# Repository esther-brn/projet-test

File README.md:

# 4GP 2024/2025 - Projet de capteur *low-tech en graphite* - Par Esther BOIRON et Margot HERNANDEZ
-------------------------

## Table des matières
* [Contacts](#contacts) 
* [Contexte](#contexte) 
* [Livrable](#livrable) 
* [Matériel requis](#matériel-requis) <br>
* [1. Simulation électronique sous LTSpice](#1-simulation-électronique-sous-ltspice) <br>
* [2. Design du PCB sous Kicad](#2-design-du-pcb-sous-kicad) <br>
* [3. Code sur Arduino](#3-code-sur-arduino) <br>
* [4. Application Android](#4-application-android) <br>
* [5. Réalisation du shield](#5-réalisation-du-shield) <br>
* [6. Banc de tests](#6-banc-de-tests) <br>
* [7. Résultats et discussion](#7-résultats-et-discussion) <br>
* [8. Datasheet du capteur](#8-datasheet-du-capteur) 
* [Conclusion](#conclusion)
------------
## Contacts
Esther BOIRON : eboiron@insa-toulouse.fr  
Margot HERNANDEZ : mhernan2@insa-toulouse.fr

------------
## Contexte
Dans le cadre de l’UF de quatrième année du département Génie Physique intitulée *Du capteur au banc de test*, nous avons développé et évalué la performance d’un capteur low-tech en graphite. Il est constitué d’un simple morceau de papier recouvert d’une trace de crayon à papier, formant une fine couche de graphite. Lorsque le papier se déforme, le nombre de particules de graphite reliées varie, entraînant une modification de la résistance du capteur. Ce phénomène permet ainsi de mesurer la déformation, à la manière d’une jauge de contrainte traditionnelle.

Ce travail s’appuie sur les recherches de scientifiques américains (Cheng-Wei Lin*, Zhibo Zhao*, Jaemyung Kim & Jiaxing Huang), qui ont publié en 2014 l’article [Pencil Drawn Strain Gauges and Chemiresistors on Paper](https://www.researchgate.net/publication/259846610_Pencil_Drawn_Strain_Gauges_and_Chemiresistors_on_Paper).

Vous trouverez ici l’ensemble des réalisations effectuées dans le cadre de ce projet : simulations électroniques, conception du PCB, programmation Arduino, développement d’une application Android et élaboration d’une datasheet.

------------
## Livrable
Plusieurs livrables sont attendus :

✓ Un shield PCB connecté à une carte Arduino UNO, intégrant : un capteur en graphite, un montage amplificateur transimpédance, un module Bluetooth, un écran OLED, un encodeur rotatif, un potentiomètre numérique ainsi qu'un capteur de flexion commercial (flex sensor).<br>

✓ Un code Arduino assurant le contrôle de l’ensemble des composants et la réalisation des mesures.<br>

✓ Une application Android permettant de visualiser les mesures depuis un smartphone.<br>

✓ Un code Arduino dédié aux essais du capteur sur le banc de test.<br>

✓ Une datasheet détaillant les caractéristiques du capteur en graphite.<br>

------------
## Matériel requis
Afin de réaliser notre dispositif, voici la liste des composants nécessaires :

Pour le montage amplificateur transimpédance :

* Des résistances : 1 de 1 kΩ, 1 de 10 kΩ, 2 de 100 kΩ
* Un potentiomètre numérique : ici, le MCP41050
* Des condensateurs : trois de 100 nF et un de 1 μF
* Un amplificateur opérationnel : ici, le LTC1050

Pour le reste du dispositif :
* Un module Bluetooth : ici, le HC05
* Un écran OLED : ici, un écran de dimensions 128x64
* Un encodeur rotatif
* Un capteur de flexion (flex sensor)
* Une résistance de 33 kΩ
* Une carte Arduino UNO
------------
## 1. Simulation électronique sous LTSpice
Notre objectif est de mesurer la résistance de notre capteur en graphite puis de retrouver sa déformation par une relation de proportionalité. Nous savons que la résistance est de l’ordre du gigaohm (GΩ). Sous une tension de 5V, correspondant à celle délivrée par l’Arduino, le capteur délivre un courant extrêmement faible, de l’ordre de quelques nanoampères (nA). Cette mesure ne peut donc pas se faire directement : nous devons amplifier le signal. De plus, nous utilisons l'Arduino Uno et ce microcontrôleur ne peut mesurer que des tensions (cf [datasheet](https://docs.arduino.cc/resources/datasheets/A000066-datasheet.pdf)). Nous avons donc besoin d'un montage amplificateur transimpédance pour convertir notre courant en une tension exploitable par les entrées analogiques de l'Arduino. Pour cela, nous avons choisi l’amplificateur opérationnel  LTC1050.

Associé à cet amplificateur, nous réalisons un montage structuré en trois zones principales qui correspondent à des filtres pour améliorer la qualité du signal mesuré :

* Filtrage en entrée de l'amplificateur (R1 et C1) : un filtre passe-bas passif de fréquence de coupure de 16 Hz qui permet de filtrer le bruit en courant sur le signal d'entrée
* Filtrage couplé à l'amplificateur (R3 et C4) : un filtre passe-bas actif de fréquence de coupure de 1.6 Hz qui permet de filtrer la composante 50 Hz issue du réseau électrique 
* Filtrage à la sortie de l'amplificateur (R6 et C2) : filtre passe bas passif de fréquence de coupure de 1.6 kHz qui permet de réduire le bruit créé lors du traitement du signal (bruits des alimentations, de l’horloge…)

Afin de pouvoir ajuster dynamiquement le gain de l’amplificateur en fonction des besoins de mesure, la résistance R2 sera remplacée ultérieurement par un potentiomètre digital.

Nous avons validé notre montage sur LTSpice en deux étapes :

Tout d'abord, nous avons réalisé une première simulation afin de s’assurer que l’amplification fonctionne correctement. L’image ci-dessous montre que le signal est bien amplifié à 1 V : le signal a donc une valeur suffisante pour être interprété par l’Arduino.

Ensuite, nous avons réalisé une seconde simulation afin d'observer la réponse à un courant alternatif afin de vérifier l’efficacité du filtrage. Les variations de la phase observées sur le graphe ci-dessous illustrent le passage du signal à travers les trois filtres successifs.

------------
## 2. Design du PCB sous Kicad
Après avoir réalisé les simulations sur LTSpice, nous avons conçu notre PCB à l’aide du logiciel KiCad. Pour cela, nous sommes parties du schéma du montage décrit précédemment, auquel nous avons apporté quelques modifications.
Parmi ces modifications, nous avons notamment remplacé la résistance R2 par un potentiomètre numérique permettant un réglage précis du gain de l’amplificateur, tout en évitant la saturation. Nous avons également ajouté plusieurs composants afin d’améliorer les fonctionnalités de notre système et de comparer les résultats obtenus :
* Le module Bluetooth HC-05 : permet d'assurer la communication entre le PCB et un smartphone via une application Android.
* Un écran OLED : utilisé pour afficher différents menus en temps réel.
* Un encodeur rotatif : contrôle la navigation entre les différentes options affichées sur l’écran OLED.
* Un flex sensor : utilisé pour comparer les mesures du capteur en graphite avec celles d’un capteur commercial lors des tests finaux

__Création des bibliothèques et symboles__  

La première étape de la conception a consisté à créer notre propre bibliothèque de symboles pour les composants spécifiques du montage. Nous avons dessiné les symboles correspondants aux différents composants utilisés. L’image ci-dessous illustre, par exemple, le symbole de l’écran OLED.

__Création des empreintes des composants__

La deuxième étape a consisté à créer les empreintes des composants. Cette phase est essentielle pour garantir une bonne intégration des composants sur le circuit imprimé. Pour cela, nous avons pris en compte la dimension physique des composants ainsi que le diamètre des trous. L’image ci-dessous illustre l’empreinte de l’écran OLED.

Afin d’obtenir une visualisation 3D réaliste de notre PCB final, nous avons associé à chaque empreinte une modélisation 3D du composant correspondant. Cette étape permet de vérifier l’agencement des composants, d’anticiper d’éventuels problèmes d’encombrement et d’optimiser le design du circuit imprimé.
Les modèles 3D utilisés ont été récupérés sur la plateforme GrabCAD, qui propose une large bibliothèque de fichiers compatibles avec KiCad.
L’image ci-dessous illustre la modélisation 3D de l’écran OLED.

__Création de la schématique électrique__

Après avoir défini les empreintes et les modèles 3D des composants, nous avons procédé à la création de la schématique électrique du montage. Lors de cette étape, nous avons opté pour un modèle basé sur l’Arduino UNO afin de garantir la correspondance correcte des pins de connexion avec l’Arduino.

__Disposition des composants sur le PCB__

La dernière étape de notre conception a été l’agencement des composants sur le PCB. L’objectif principal est d’optimiser leur disposition en tenant compte des connexions électriques tout en minimisant l’utilisation de vias. Les images ci-dessous présentent le résultat final de notre PCB, ainsi que sa vue en 3D, permettant de visualiser l’implantation des composants.

------------
## 3. Code sur Arduino
Notre code Arduino, conçu pour contrôler les composants implémentés et effectuer les mesures à l’aide du capteur en graphite et du capteur commercial, a été développé sous [Arduino IDE 2.3.4](https://www.arduino.cc/en/software/).  

Nous avons utilisé les bibliothèques *SoftwareSerial.h* pour la communication Bluetooth et *Adafruit_SSD1306.h* pour l'affichage sur écran OLED. Étant donné que notre programme utilise une part importante de la mémoire RAM, nous avons rencontré des problèmes de stockage : le programme ne se lançait pas et aucune information n'était affichée dans l'IDE lors du téléversement. Pour remédier à cela, nous avons intégré la bibliothèque *avr/pgmspace.h*, qui permet de stocker des données en mémoire flash afin de libérer de l’espace dans la RAM. 

Nous avons réalise un premier programme qui permet de calibrer le potentiomètre digitale afin d’optimiser les mesures réalisées par les deux capteurs. Le programme principal propose une interface à l’écran avec quatre menus, accessibles en tournant l’encodeur rotatif. La sélection d’un menu se fait en appuyant sur le bouton intégré à l’encodeur. Ce bouton permet également de revenir au menu principal lorsque nous sommes dans un sous-menu.  

Les sous-menus disponibles sont les suivants :
* Menu Informations : fournit des détails sur le projet.
* Menu Application : permet d'établir une communication avec l’application Android via le module Bluetooth.
* Menu Capteur Graphite : affiche en temps réel la valeur de résistance mesurée par le capteur en graphite.
* Menu Capteur Commercial : affiche en temps réel la valeur de résistance mesurée par le capteur commercial.<br>

Les codes complets sont disponibles dans le dossier [Arduino](Arduino).

Ci-dessous, une vidéo illustrant les différents menus accessibles sur l’écran OLED :

------------
## 4. Application Android
Nous avons également réalisé une application Android développée sous [MIT App Inventor](https://appinventor.mit.edu/).

Cette application reçoit les données transmises par le module Bluetooth HC-05 lorsque l’utilisateur est dans le mode « application » de l’écran OLED accessible via l’encodeur rotatif. 

Deux modes sont disponibles à partir d’un listpicker : le mode « capteur graphite » et le mode « capteur commercial ». Dans chacun de ces modes, la valeur de la résistance du capteur est affichée en temps réel. En cliquant sur le bouton « start », l’application passe en mode acquisition et trace l’évolution de la résistance sur un graphique en fonction du temps. L’acquisition est arrêtée en cliquant sur « pause ». Le bouton refresh permet de réinitialiser le graphique en effaçant les données précédemment tracées.

L’application ainsi que son code source sont disponibles dans le répertoire [Application](Application).

------------
## 5. Réalisation du shield
Après la conception et la validation du PCB, nous avons procédé à la fabrication physique du shield en suivant plusieurs étapes :
* Vérification du PCB sur KiCad : utilisation de l’outil Contrôle des règles de conception (DRC) pour s’assurer qu’il n’y a pas d’erreur dans les connexions et les espacements des pistes.
* Impression du masque de gravure sur un papier transparent 
* Insolation UV d’une plaquette d’époxy recouverte d’une couche de cuivre et de résine photosensible : la plaquette est exposée aux UV à travers le masque
* Révélation du motif : la plaquette est immergée dans un révélateur (soude très diluée) afin d'éliminer la résine exposée aux UV et laisser les pistes de cuivre protégées 
* Gravure des pistes : la plaquette est immergée dans un bain de perchlorure de fer pour graver les pistes
* Nettoyage de la plaquette : utilisation d'acétone pour retirer les résidus de résine 
* Perçage des trous et soudure des composants sur le PCB

------------
## 6. Banc de tests
Le but de ce banc de test est de déterminer la sensibilité du capteur, d’étudier son évolution, puis de la comparer à celle d’un capteur commercial de type "Flex-Sensor". Pour cela, nous avons utilisé le banc de test suivant, composé de six cercles dont les diamètres varient de 1.4 à 3.9 cm. Ce banc a été fabriqué à l’aide d’une imprimante 3D.

Ce banc de test permet de mesurer la variation de résistance relative ΔR/R0 en fonction de la déformation ε, définie par la relation ε =e/D où e est l'épaisseur du capteur (ici celle de la feuille, soit 0,2 mm) et D le diamètre du cercle considéré.  

Les tests ont été réalisés en tension et en compression sur des capteurs à base de graphite.

Ces capteurs ont été fabriqués à l’aide de quatre types de graphite différents : des crayons 6B, 4B, B et HB. Pour maintenir les capteurs en papier sur le banc de test sans les toucher pendant les mesures, nous avons utilisé de la pâte à fixe.

------------
## 7. Résultats et discussion
Les courbes ci-dessous illustrent les variations de la résistance en fonction de la déformation, en tension et en compression, pour des capteurs en graphite réalisés avec différents types de crayons. 

La courbe ci-dessous présente le comportement du capteur commercial pour une déformation en tension, le flex sensor ne supportant pas une déformation en compression. 

On remarque que lorsque le capteur graphite est soumis à une déformation en tension, la résistance du capteur augmente. Ce phénomène est attendu : en tension, les distances entre les nanoparticules de graphite s’allongent, ce qui freine le passage du courant et augmente la résistance. A l’inverse, lors d’une compression, les grains se rapprochent, facilitant le passage du courant et donc la résistance diminue.  

Les résultats montrent aussi que le type de crayon utilisé influence fortement les valeurs de résistance mesurées. Plus un crayon est gras (comme le 6B ou le 4B), plus il dépose de graphite sur le papier, ce qui réduit la résistance globale du capteur. Les courbes indiquent également que plus un crayon est gras, moins la variation relative de la résistance est importante. Autrement dit, les capteurs réalisés avec des crayons plus gras sont moins sensibles à la déformation.  

Ces résultats expérimentaux permettent de conclure que le capteur commercial est globalement plus sensible à la déformation que les capteurs en graphite. De plus, il présente une bien meilleure robustesse : les capteurs en graphite sont fragiles et le simple fait de toucher leur surface peut altérer le dépôt de graphite, faussant les mesures qui suivent. Il faut les manipuler avec beaucoup de précaution. Leur durée de vie est aussi limitée, en particulier lorsqu’ils sont soumis à de fortes déformations. Entre chaque série de tests (tension ou compression), il a été nécessaire de fabriquer un nouveau capteur, car la résistance au repos changeait significativement après les premières déformations.  

Il est important de noter que plusieurs facteurs peuvent influencer les résultats, notamment la quantité de graphite déposée sur le papier, qui est difficile à maîtriser précisément. Cette variabilité peut entraîner des écarts non négligeables dans les mesures. Une amélioration possible consisterait à développer un procédé de dépôt de graphite d’une quantité fixe et reproductible, ainsi qu’un système de protection de la face du capteur contenant le trait de graphite pour éviter la perte de matière au contact.  

Le capteur commercial s'avère donc plus précis, plus robuste, et mieux adapté à des mesures répétées ou à des déformations importantes. En revanche, les capteurs en graphite présentent l’avantage de pouvoir mesurer des déformations en compression, contrairement au flex-sensor.

------------
## 8. Datasheet du capteur
Vous pouvez trouver la datasheet du capteur [ici](Datasheet.pdf).

------------
## Conclusion
Ce projet a été très enrichissant, nous offrant une immersion concrète dans le métier d’ingénieur, avec des tâches variées allant des phases de simulation jusqu’à la rédaction d’une datasheet. Nous avons apprécié la diversité des compétences mobilisées : conception électronique, fabrication, expérimentation et analyse, ainsi que la satisfaction de voir aboutir un produit final fonctionnel.  

Le capteur que nous avons développé est opérationnel et les tests réalisés mettent en évidence des tendances globalement cohérentes avec les principes physiques attendus. Ces résultats montrent qu’un simple matériau comme le graphite peut être exploité pour détecter des déformations mécaniques.  

Cependant, les conditions expérimentales mises en œuvre restent assez artisanales et peu reproductibles. La précision des mesures est fortement influencée par des paramètres difficilement maîtrisables, tels que la quantité de graphite déposée ou la qualité du contact des pinces sur les traits de crayon du capteur. De plus, la fragilité du capteur et sa très faible durée de vie rendent son industrialisation peu envisageable.

<br><br><br><br><br>

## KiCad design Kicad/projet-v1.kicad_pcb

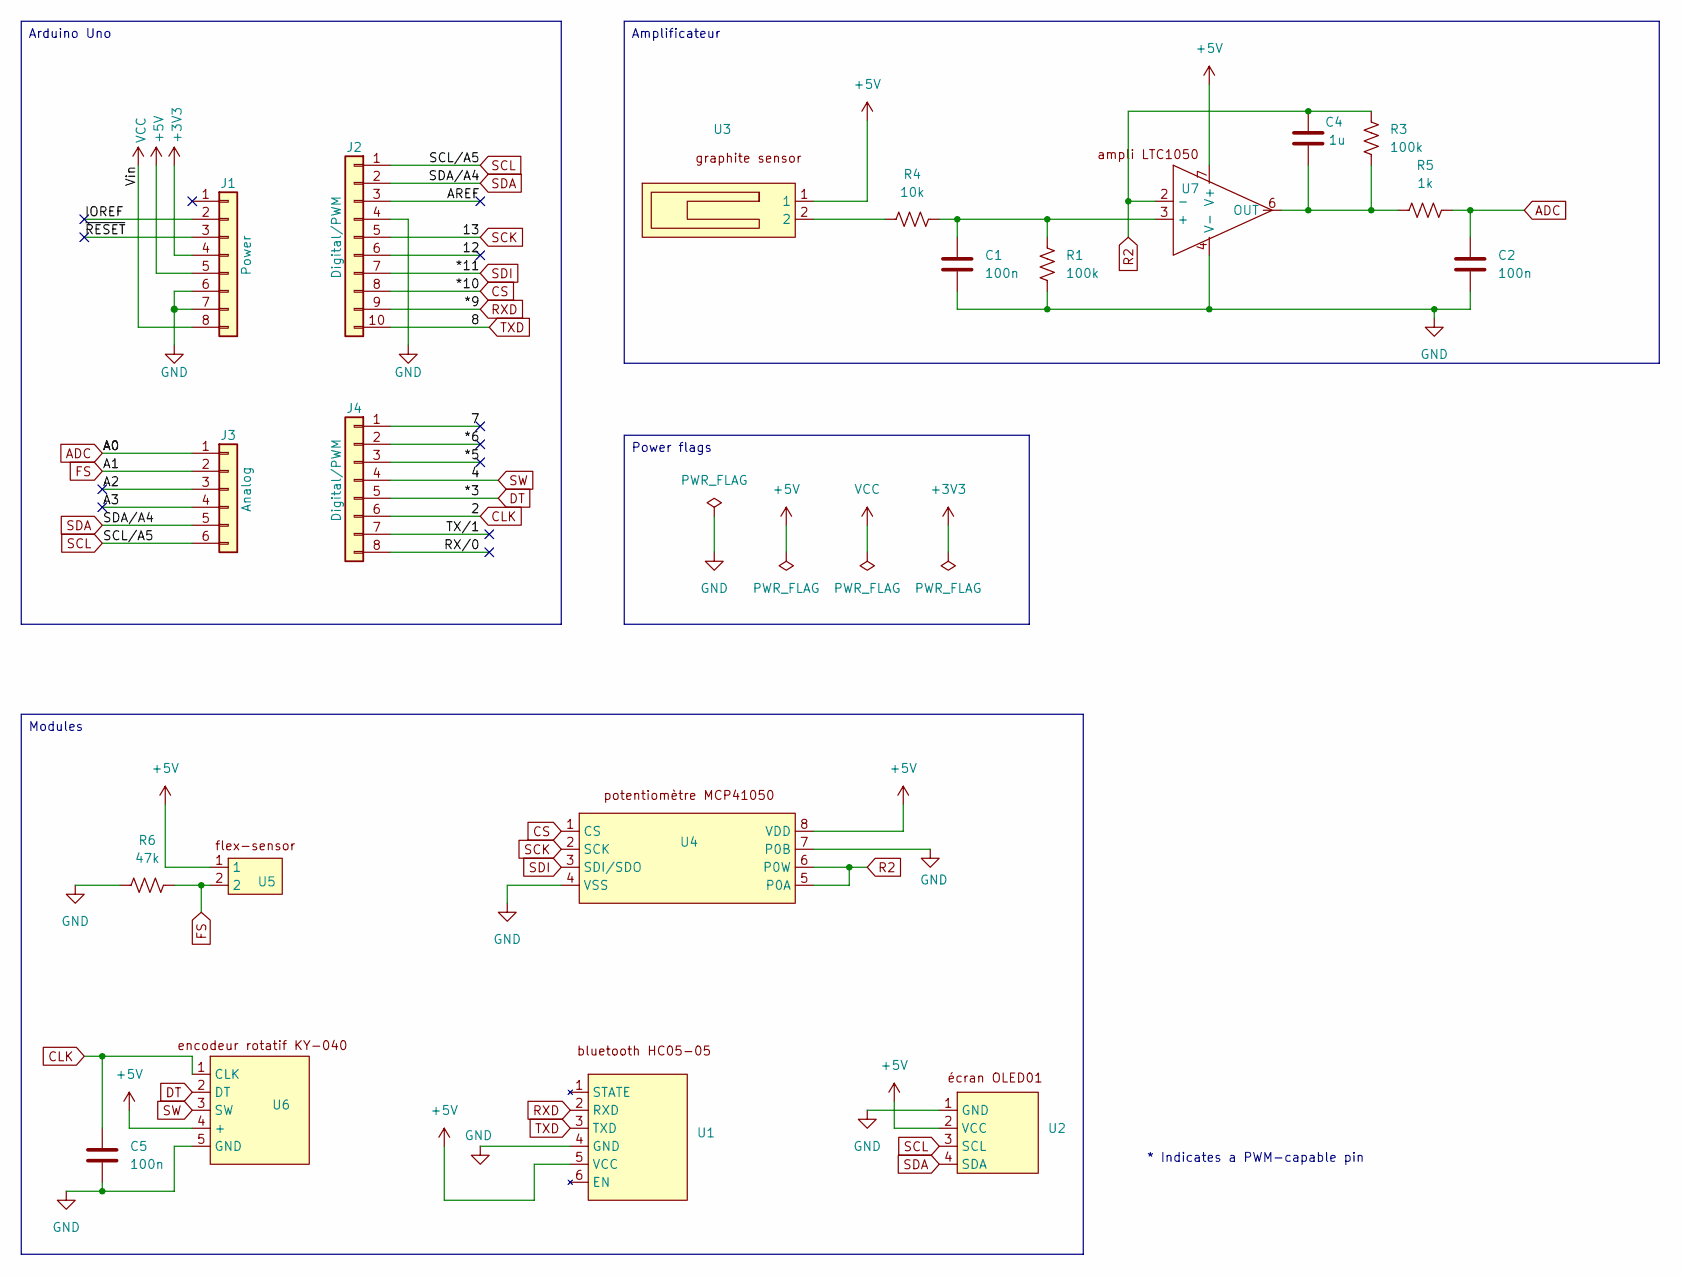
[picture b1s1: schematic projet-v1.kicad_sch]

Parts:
C1, C2, C5: 100n; C_Disc_D4.7mm_W2.5mm_P5.00mm
C4: 1u; C_Rect_L7.0mm_W4.5mm_P5.00mm
J1: Power; PinSocket_1x08_P2.54mm_Vertical
J2: Digital/PWM; PinSocket_1x10_P2.54mm_Vertical
J3: Analog; PinSocket_1x06_P2.54mm_Vertical
J4: Digital/PWM; PinSocket_1x08_P2.54mm_Vertical
R1, R3: 100k; R_Axial_DIN0207_L6.3mm_D2.5mm_P5.08mm_Vertical
R4: 10k; R_Axial_DIN0207_L6.3mm_D2.5mm_P5.08mm_Vertical
R5: 1k; R_Axial_DIN0207_L6.3mm_D2.5mm_P5.08mm_Vertical
R6: 47k; R_Axial_DIN0207_L6.3mm_D2.5mm_P5.08mm_Vertical
U1: HC05-05
U2: OLED01
U3: graphite-sensor
U4: MCP41050
U5: flex-sensor
U6: KY-040
U7: LTC1050

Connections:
+3V3: J1.4
+5V: J1.5, U1.5 (VCC), U2.2 (VCC), U3.1, U4.8 (VDD), U5.1, U6.4 (+), U7.7 (V+)
/7: J4.1
/12: J2.6
/*5: J4.3
/*6: J4.2
/A2: J3.3
/A3: J3.4
/AREF: J2.3
/IOREF: J1.2
/RX/0: J4.8
/TX/1: J4.7
/~RESET: J1.3
ADC: C2.1, J3.1, R5.2
CLK: C5.1, J4.6, U6.1 (CLK)
CS: J2.8, U4.1 (CS)
DT: J4.5, U6.2 (DT)
FS: J3.2, R6.2, U5.2
GND: C1.2, C2.2, C5.2, J1.6, J1.7, J2.4, R1.2, R6.1, U1.4 (GND), U2.1 (GND), U4.4 (VSS), U4.7 (P0B), U6.5 (GND), U7.4 (V-)
unnamed: R4.1, U3.2
unnamed: C1.1, R1.1, R4.2, U7.3 (+)
unnamed: C4.2, R3.2, R5.1, U7.6 (OUT)
R2: C4.1, R3.1, U4.5 (P0A), U4.6 (P0W), U7.2 (-)
RXD: J2.9, U1.2 (RXD)
SCK: J2.5, U4.2 (SCK)
SCL: J2.1, J3.6, U2.3 (SCL)
SDA: J2.2, J3.5, U2.4 (SDA)
SDI: J2.7, U4.3 (SDI/SDO)
SW: J4.4, U6.3 (SW)
TXD: J2.10, U1.3 (TXD)
VCC: J1.8

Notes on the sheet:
* Indicates a PWM-capable pin
Power flags
Amplificateur
Arduino Uno
Modules

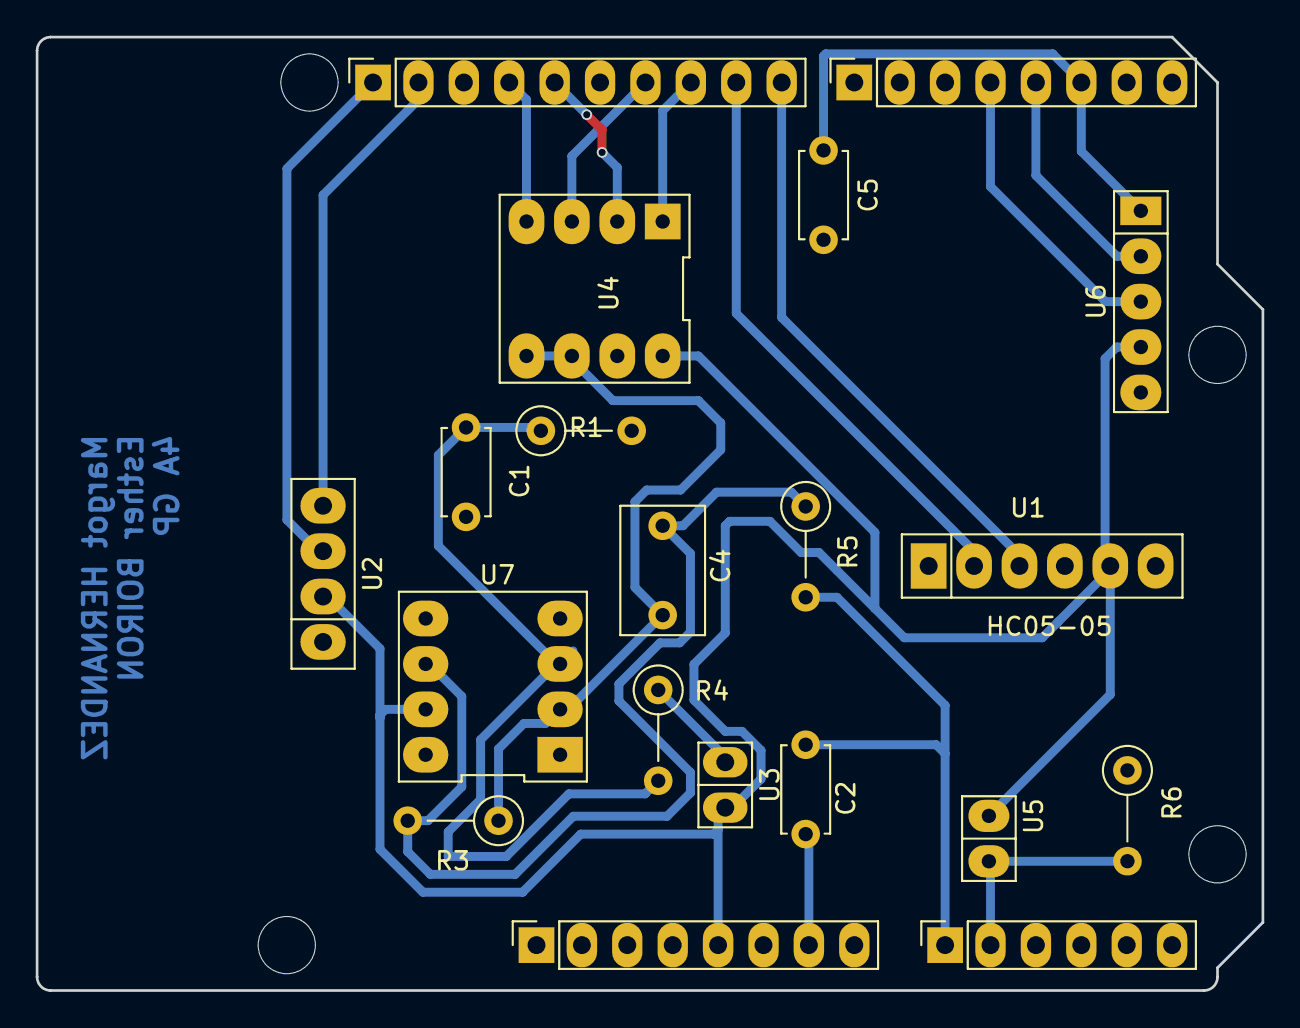
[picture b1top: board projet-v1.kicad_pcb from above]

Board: 2 copper layers, 68.6 x 53.3 mm, 24 parts (0 on the bottom side), 18 nets.

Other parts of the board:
MH1, MH2, MH3, MH4: MountingHole_3.2mm

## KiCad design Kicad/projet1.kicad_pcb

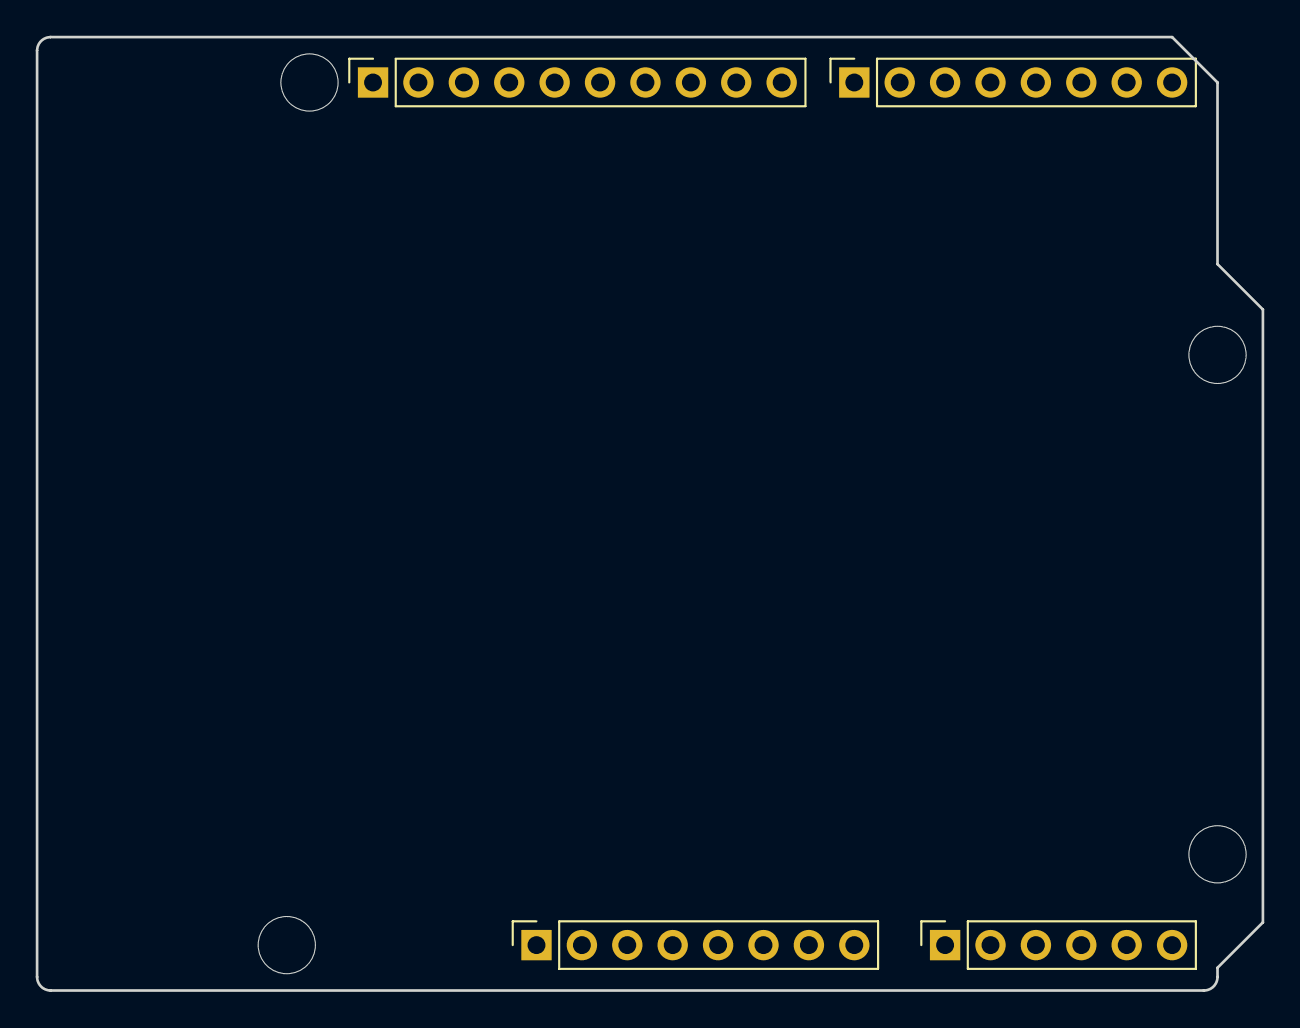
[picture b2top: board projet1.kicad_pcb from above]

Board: 2 copper layers, 68.6 x 53.3 mm, 8 parts (0 on the bottom side), 3 nets, no tracks yet.

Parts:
J1: Power; PinSocket_1x08_P2.54mm_Vertical
J2: Digital/PWM; PinSocket_1x10_P2.54mm_Vertical
J3: Analog; PinSocket_1x06_P2.54mm_Vertical
J4: Digital/PWM; PinSocket_1x08_P2.54mm_Vertical
MH1, MH2, MH3, MH4: MountingHole_3.2mm

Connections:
/SCL/A5: J2.1, J3.6
/SDA/A4: J2.2, J3.5
GND: J1.6, J1.7, J2.4

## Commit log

2025-03-20 Premier commit
2025-03-20 MAJ README.md
2025-03-23 MAJ dossier image
2025-03-23 MAJ README v2
2025-03-26 MAJ README v3
2025-04-06 MAJ README v4
2025-04-08 MAJ README v5
2025-04-11 MAJ README v6
2025-04-15 Update README.md
    J'ai ajouté "commercial" pour le capteur
2025-04-15 Update README.md 2
    Quelques modifs dans la partie "Simulation électronique sous LTSpice". Dans le texte de base tu dis que l'arduino ne peut pas mesurer des courants aussi faibles. Mais il me semble qu'il ne mesure pas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
2025-04-15 Update README.md 3
    juste des petites fautes d'orthopgraphe
2025-04-15 Update README.md 5
    Dans la partie Kicad : à la fin de chaque étape tu expliques l'étape suivante mais du coup dans l'étape suivante tu redis la même chose. Je sais pas si c'est voulu ou si c'est un souci de copié collé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
2025-04-15 Update README.md 6
    Encore un peti copié-collé qui s'était perdu
